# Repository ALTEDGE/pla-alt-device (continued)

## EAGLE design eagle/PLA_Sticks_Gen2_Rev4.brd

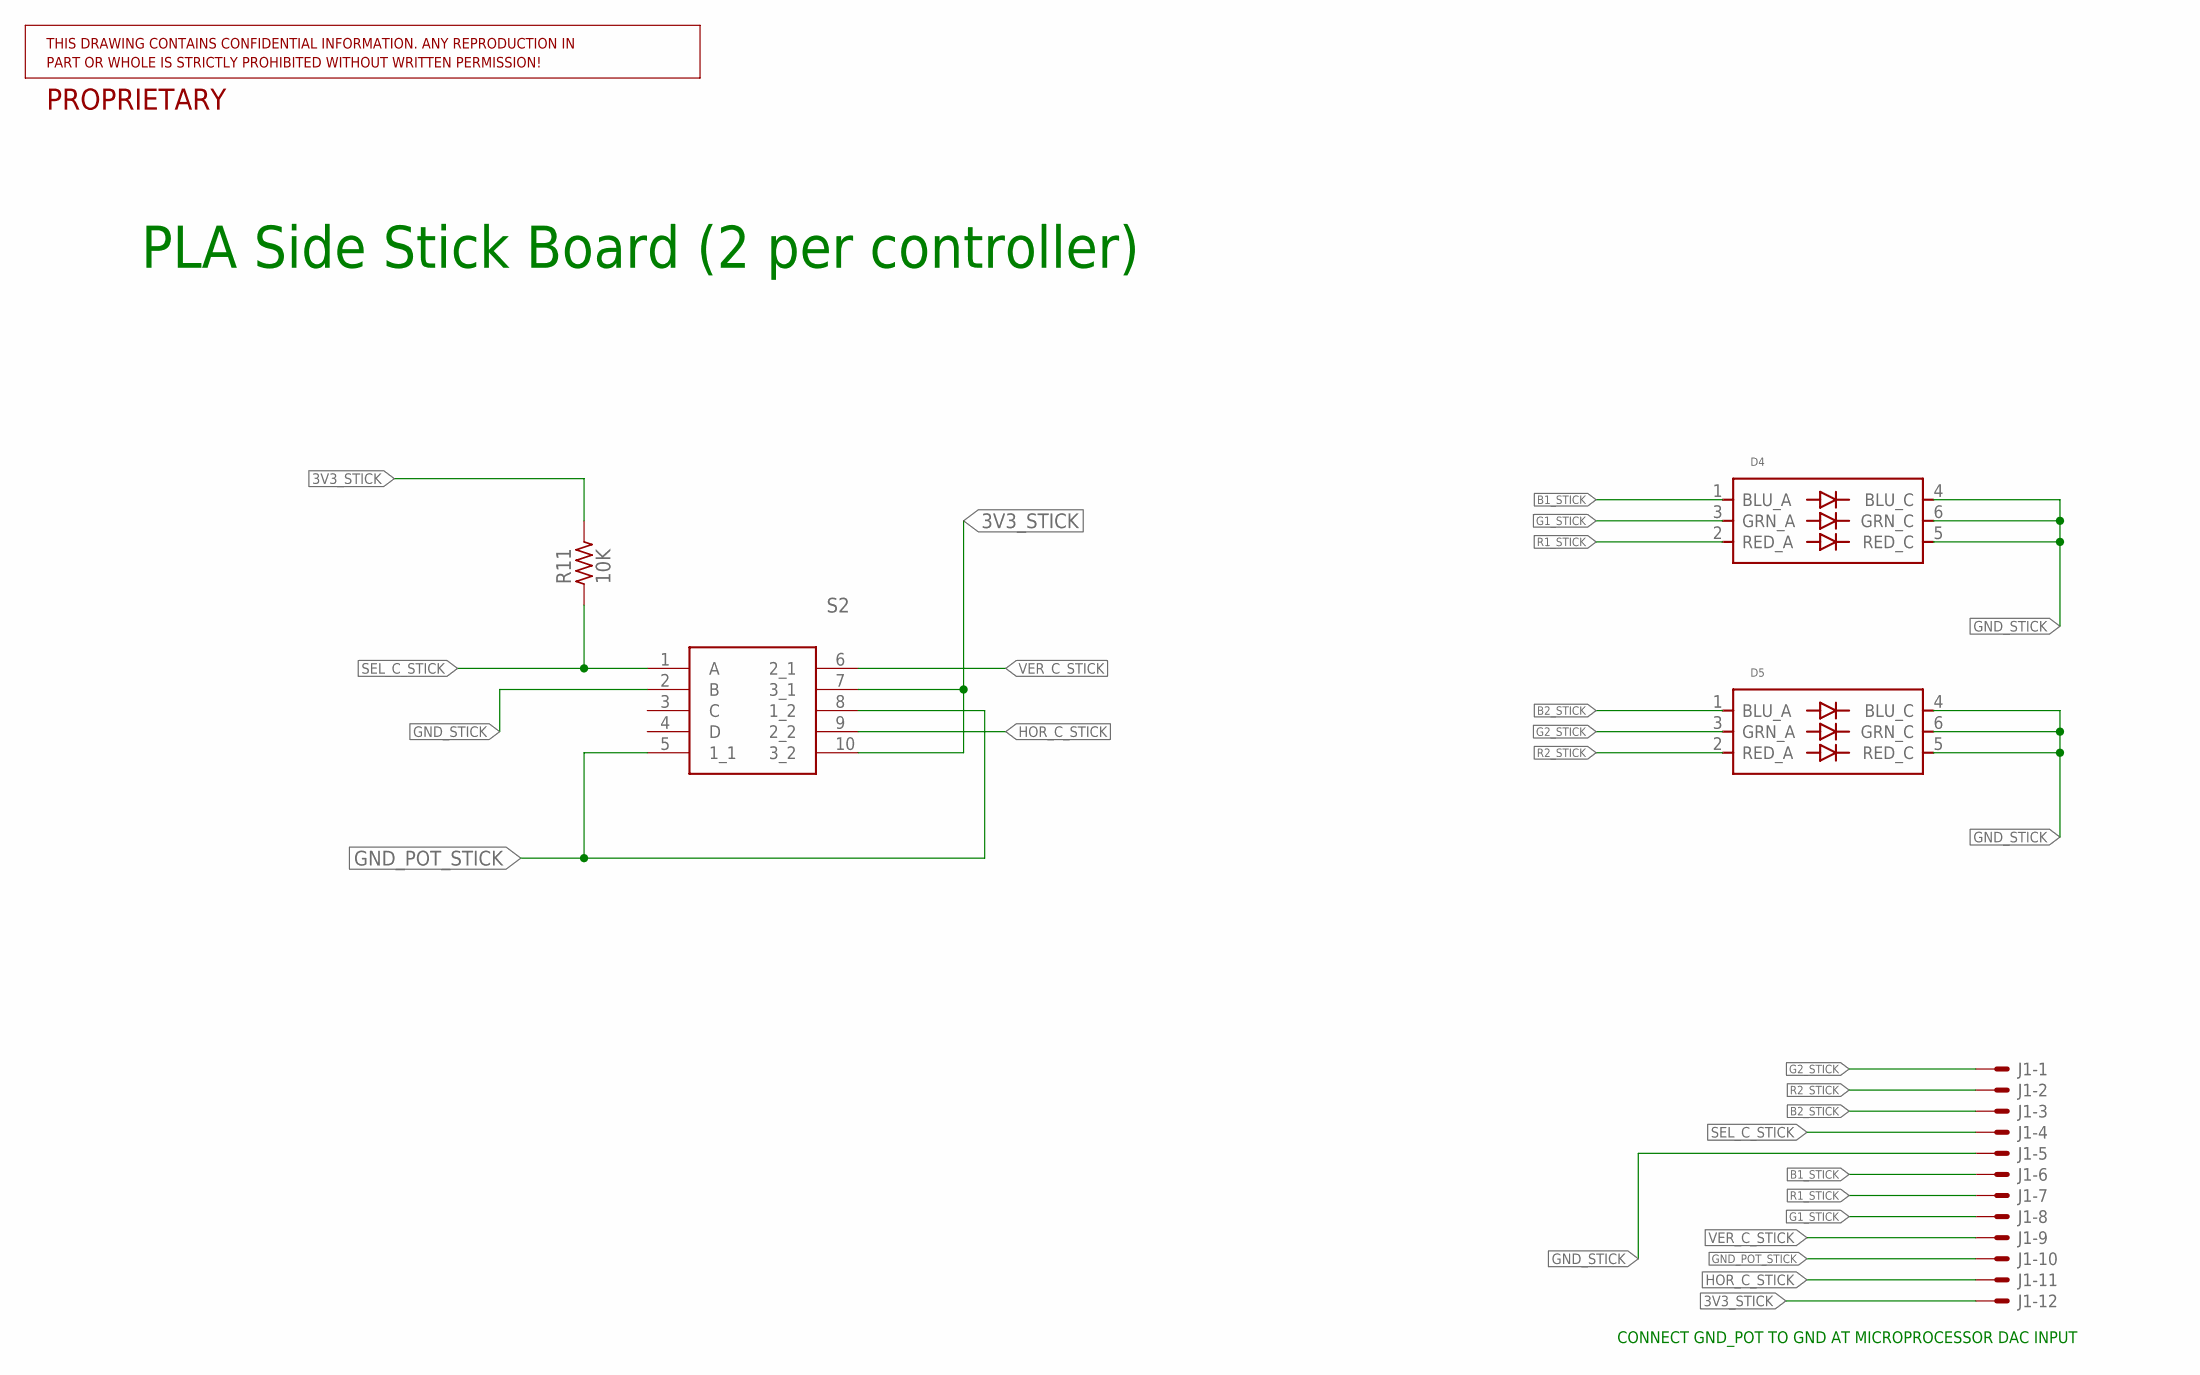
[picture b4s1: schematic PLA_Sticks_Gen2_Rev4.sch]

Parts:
D4, D5: XZFBBM2ACRDG92W-3; PARTNO XZFBBM2ACRDG92W-3
J1: SM12B-SSR-H-TB; PARTNO BM12B-SRSS-TB(LF)(SN)
R11: 10K; R0603; PARTNO ERJ-2GEJ103X
S2: RKJXV1224005; PARTNO RKJXV1224005

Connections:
3V3_STICK: J1.12, R11.2, S2.7 (3_1), S2.10 (3_2)
B1_STICK: D4.1 (BLU_A), J1.6
B2_STICK: D5.1 (BLU_A), J1.3
G1_STICK: D4.3 (GRN_A), J1.8
G2_STICK: D5.3 (GRN_A), J1.1
GND_POT_STICK: J1.10, S2.5 (1_1), S2.8 (1_2)
GND_STICK: D4.4 (BLU_C), D4.5 (RED_C), D4.6 (GRN_C), D5.4 (BLU_C), D5.5 (RED_C), D5.6 (GRN_C), J1.5, S2.2 (B)
HOR_C_STICK: J1.11, S2.9 (2_2)
R1_STICK: D4.2 (RED_A), J1.7
R2_STICK: D5.2 (RED_A), J1.2
SEL_C_STICK: J1.4, R11.1, S2.1 (A)
VER_C_STICK: J1.9, S2.6 (2_1)

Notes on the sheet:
CONNECT GND_POT TO GND AT MICROPROCESSOR DAC INPUT
PLA Side Stick Board (2 per controller)

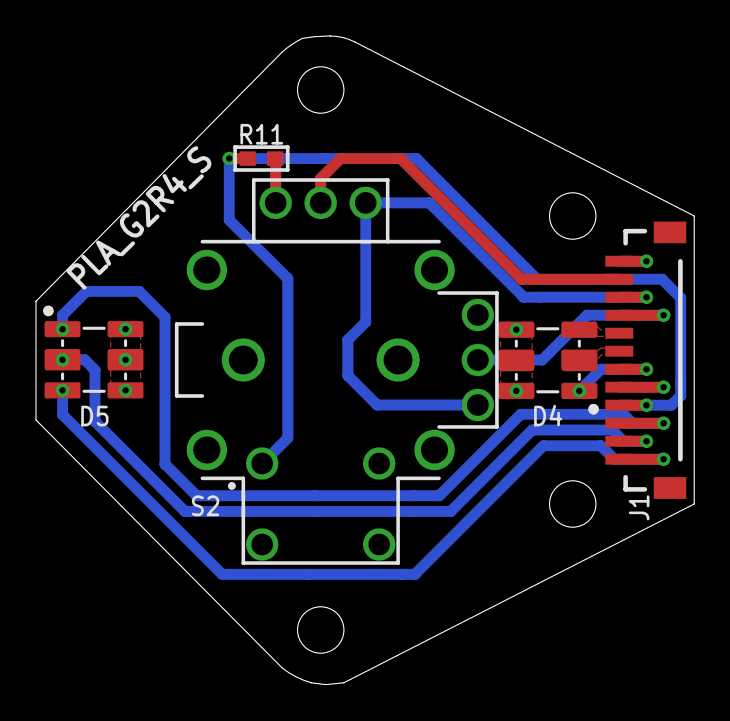
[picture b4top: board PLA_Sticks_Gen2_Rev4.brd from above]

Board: 4 copper layers, 36.6 x 36.0 mm, 11 parts (0 on the bottom side), 12 nets.

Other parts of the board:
U$3: FAB_FRAME_ANSI-A
U$4: FAB_DOCFIELD_GENERIC
U$6, U$7, U$8, U$9: 101-NS

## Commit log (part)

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2019-06-13 better analog steering
2019-07-24 restructured code and added documentation
2019-07-29 connect/disconnect updates
2019-08-06 fixed joystick/wheel ranges
2021-01-06 add test mode
2021-01-08 fix test mode color overflow; fix indentation
2021-06-10 fix for prod. proto.; improve debug
2021-06-17 wheel calibration; idle sleep; faster update rate
2021-07-07 add modified bootloader for usb programming
2021-07-28 minimized bootloader; joystick calibration
2021-07-29 add hardware folder
2021-07-29 add build instructions
2021-08-10 store calib in eeprom
2021-08-13 query pg; fix id response
2021-08-19 color fix; send joy state once per loop
2021-08-19 improve wheel accuracy
2021-08-20 wheel: improved oversampling/deadzone
2021-08-23 Remove wheel averaging
2021-08-24 license and readme update
2021-08-25 upload eagle files
2021-08-25 add hardware notes
2021-08-25 specify TAPR license for hardware files
2021-09-07 lower idle color intensity
2021-09-07 BUILD.md: link to ALTEDGE repo
2021-09-13 use new usb id
2021-09-22 allow PG control over serial
2025-10-28 support additional leds
2025-12-31 change USB name to FPS; support individual led settings
